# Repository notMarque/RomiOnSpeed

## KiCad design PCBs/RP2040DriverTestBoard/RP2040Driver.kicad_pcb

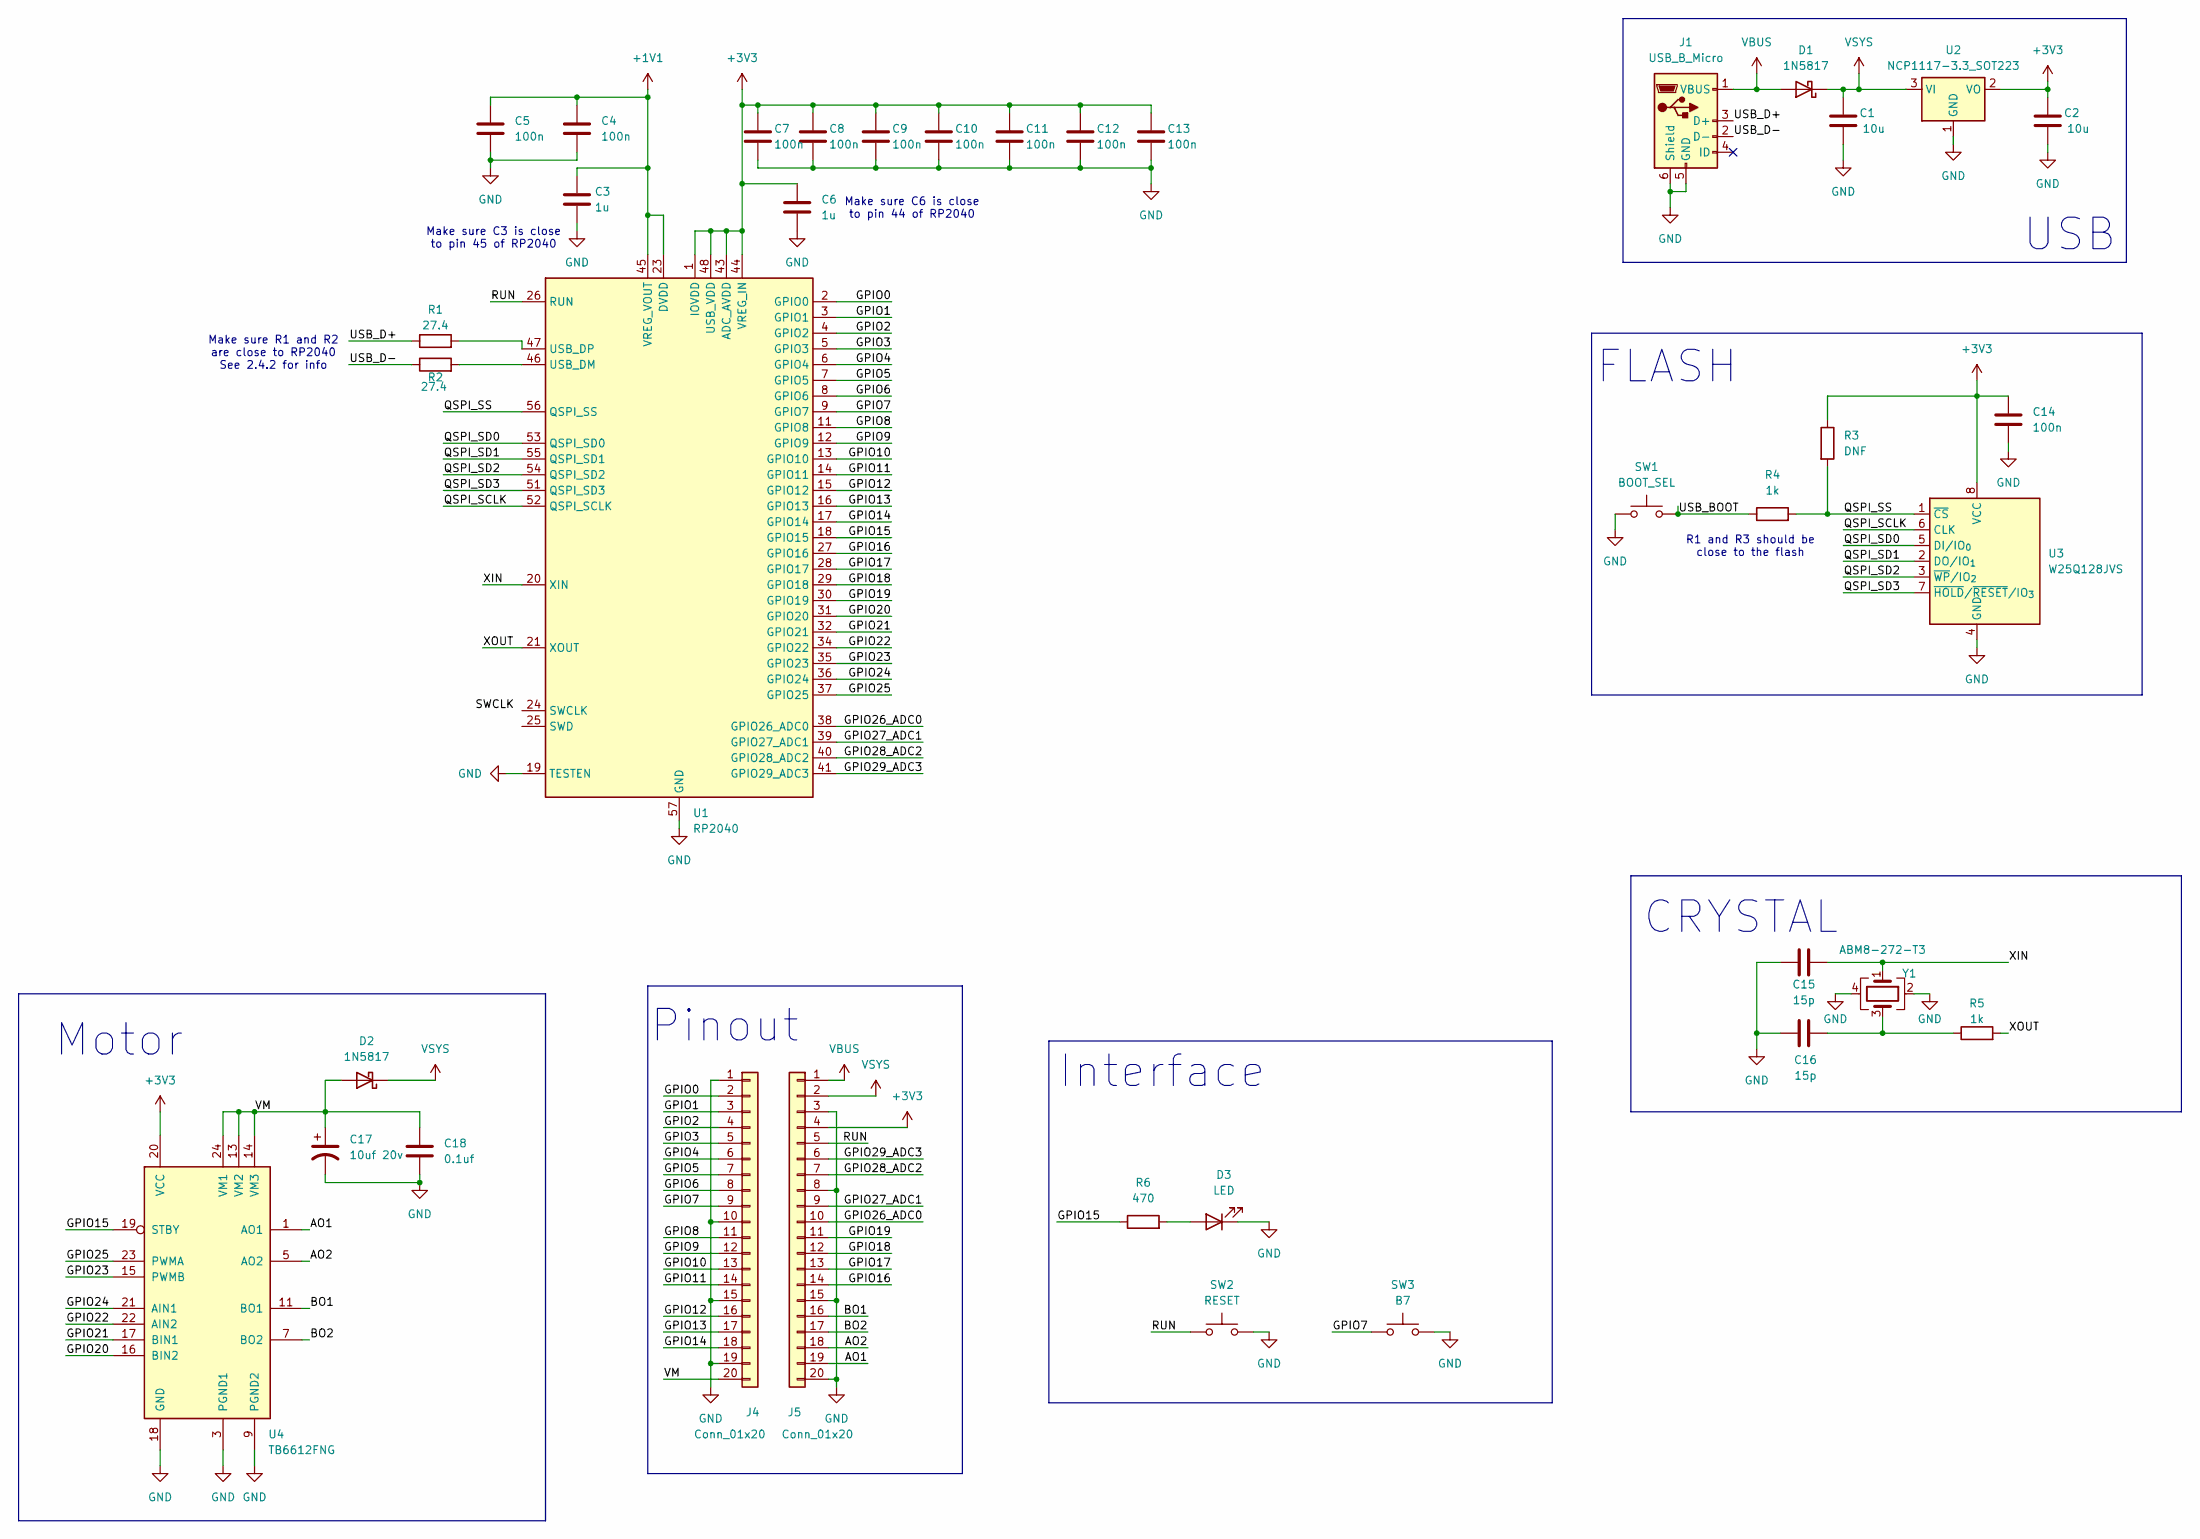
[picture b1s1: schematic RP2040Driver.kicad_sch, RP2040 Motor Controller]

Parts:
C1, C2: 10u; C_0603_1608Metric_Pad1.08x0.95mm_HandSolder
C3, C6: 1u; C_0603_1608Metric_Pad1.08x0.95mm_HandSolder
C4, C5, C7, C8, C9, C10, C11, C12, C13, C14: 100n; C_0603_1608Metric_Pad1.08x0.95mm_HandSolder
C15, C16: 15p; C_0603_1608Metric_Pad1.08x0.95mm_HandSolder
C17: 10uf 20v; C_0603_1608Metric_Pad1.08x0.95mm_HandSolder
C18: 0.1uf; C_0603_1608Metric_Pad1.08x0.95mm_HandSolder
D1, D2: 1N5817; D_0603_1608Metric_Pad1.05x0.95mm_HandSolder
D3: LED; LED_0603_1608Metric_Pad1.05x0.95mm_HandSolder
J1: USB_B_Micro; USB_Micro-B_Amphenol_10103594-0001LF_Horizontal
J4, J5: Conn_01x20; PinHeader_1x20_P2.54mm_Vertical
R1, R2: 27.4; R_0603_1608Metric_Pad0.98x0.95mm_HandSolder
R3: DNF; R_0603_1608Metric_Pad0.98x0.95mm_HandSolder
R4, R5: 1k; R_0603_1608Metric_Pad0.98x0.95mm_HandSolder
R6: 470; R_0603_1608Metric_Pad0.98x0.95mm_HandSolder
SW1: BOOT_SEL; SW_Tactile_SPST_NO_Straight_CK_PTS636Sx25SMTRLFS
SW2: RESET; SW_Tactile_SPST_NO_Straight_CK_PTS636Sx25SMTRLFS
SW3: B7; SW_Tactile_SPST_NO_Straight_CK_PTS636Sx25SMTRLFS
U1: RP2040; QFN-56-1EP_7x7mm_P0.4mm_EP3.2x3.2mm
U2: NCP1117-3.3_SOT223; SOT-223-3_TabPin2
U3: W25Q128JVS; SOIC-8_5.3x5.3mm_P1.27mm
U4: TB6612FNG; SSOP-24_5.3x8.2mm_P0.65mm
Y1: ABM8-272-T3; Crystal_SMD_Abracon_ABM8G-4Pin_3.2x2.5mm

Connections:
+1V1: C3.1, C4.1, C5.1, U1.23 (DVDD), U1.45 (VREG_VOUT), U1.50 (DVDD)
+3V3: C2.1, C6.1, C7.1, C8.1, C9.1, C10.1, C11.1, C12.1, C13.1, C14.1, J5.4, R3.1, U1.1 (IOVDD), U1.10 (IOVDD), U1.22 (IOVDD), U1.33 (IOVDD), U1.42 (IOVDD), U1.43 (ADC_AVDD), U1.44 (VREG_IN), U1.48 (USB_VDD), U1.49 (IOVDD), U2.2 (VO), U3.8 (VCC), U4.20 (VCC)
/AO1: J5.19, U4.1 (AO1), U4.2 (AO1)
/AO2: J5.18, U4.5 (AO2), U4.6 (AO2)
/BO1: J5.16, U4.11 (BO1), U4.12 (BO1)
/BO2: J5.17, U4.7 (BO2), U4.8 (BO2)
/GPIO0: J4.2, U1.2 (GPIO0)
/GPIO1: J4.3, U1.3 (GPIO1)
/GPIO2: J4.4, U1.4 (GPIO2)
/GPIO3: J4.5, U1.5 (GPIO3)
/GPIO4: J4.6, U1.6 (GPIO4)
/GPIO5: J4.7, U1.7 (GPIO5)
/GPIO6: J4.8, U1.8 (GPIO6)
/GPIO7: J4.9, SW3.1, U1.9 (GPIO7)
/GPIO8: J4.11, U1.11 (GPIO8)
/GPIO9: J4.12, U1.12 (GPIO9)
/GPIO10: J4.13, U1.13 (GPIO10)
/GPIO11: J4.14, U1.14 (GPIO11)
/GPIO12: J4.16, U1.15 (GPIO12)
/GPIO13: J4.17, U1.16 (GPIO13)
/GPIO14: J4.18, U1.17 (GPIO14)
/GPIO15: R6.1, U1.18 (GPIO15), U4.19 (STBY)
/GPIO16: J5.14, U1.27 (GPIO16)
/GPIO17: J5.13, U1.28 (GPIO17)
/GPIO18: J5.12, U1.29 (GPIO18)
/GPIO19: J5.11, U1.30 (GPIO19)
/GPIO20: U1.31 (GPIO20), U4.16 (BIN2)
/GPIO21: U1.32 (GPIO21), U4.17 (BIN1)
/GPIO22: U1.34 (GPIO22), U4.22 (AIN2)
/GPIO23: U1.35 (GPIO23), U4.15 (PWMB)
/GPIO24: U1.36 (GPIO24), U4.21 (AIN1)
/GPIO25: U1.37 (GPIO25), U4.23 (PWMA)
/GPIO26_ADC0: J5.10, U1.38 (GPIO26_ADC0)
/GPIO27_ADC1: J5.9, U1.39 (GPIO27_ADC1)
/GPIO28_ADC2: J5.7, U1.40 (GPIO28_ADC2)
/GPIO29_ADC3: J5.6, U1.41 (GPIO29_ADC3)
/QSPI_SCLK: U1.52 (QSPI_SCLK), U3.6 (CLK)
/QSPI_SD0: U1.53 (QSPI_SD0), U3.5 (DI/IO_{0})
/QSPI_SD1: U1.55 (QSPI_SD1), U3.2 (DO/IO_{1})
/QSPI_SD2: U1.54 (QSPI_SD2), U3.3 (~WP/IO_{2})
/QSPI_SD3: U1.51 (QSPI_SD3), U3.7 (~HOLD/~RESET/IO_{3})
/QSPI_SS: R3.2, R4.2, U1.56 (QSPI_SS), U3.1 (~CS)
/RUN: J5.5, SW2.1, U1.26 (RUN)
/USB_BOOT: R4.1, SW1.2
/USB_D+: J1.3 (D+), R1.1
/USB_D-: J1.2 (D-), R2.1
/VM: C17.1, C18.1, D2.2 (A), J4.20, U4.13 (VM2), U4.14 (VM3), U4.24 (VM1)
/XIN: C15.2, U1.20 (XIN), Y1.1
/XOUT: R5.2, U1.21 (XOUT)
GND: C1.2, C2.2, C3.2, C4.2, C5.2, C6.2, C7.2, C8.2, C9.2, C10.2, C11.2, C12.2, C13.2, C14.2, C15.1, C16.1, C17.2, C18.2, D3.1 (K), J1.5 (GND), J1.6 (Shield), J4.1, J4.10, J4.15, J4.19, J5.3, J5.8, J5.15, J5.20, SW1.1, SW2.2, SW3.2, U1.19 (TESTEN), U1.57 (GND), U2.1 (GND), U3.4 (GND), U4.3 (PGND1), U4.4 (PGND1), U4.9 (PGND2), U4.10 (PGND2), U4.18 (GND), Y1.2, Y1.4
unnamed: C16.2, R5.1, Y1.3
unnamed: D3.2 (A), R6.2
unnamed: R2.2, U1.46 (USB_DM)
unnamed: R1.2, U1.47 (USB_DP)
VBUS: D1.2 (A), J1.1 (VBUS), J5.1
VSYS: C1.1, D1.1 (K), D2.1 (K), J5.2, U2.3 (VI)

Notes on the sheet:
Make sure R1 and R2 are close to RP2040 See 2.4.2 for info
Interface
FLASH
Make sure C3 is close to pin 45 of RP2040
R1 and R3 should be close to the flash
CRYSTAL
Motor
USB
Pinout
Make sure C6 is close to pin 44 of RP2040

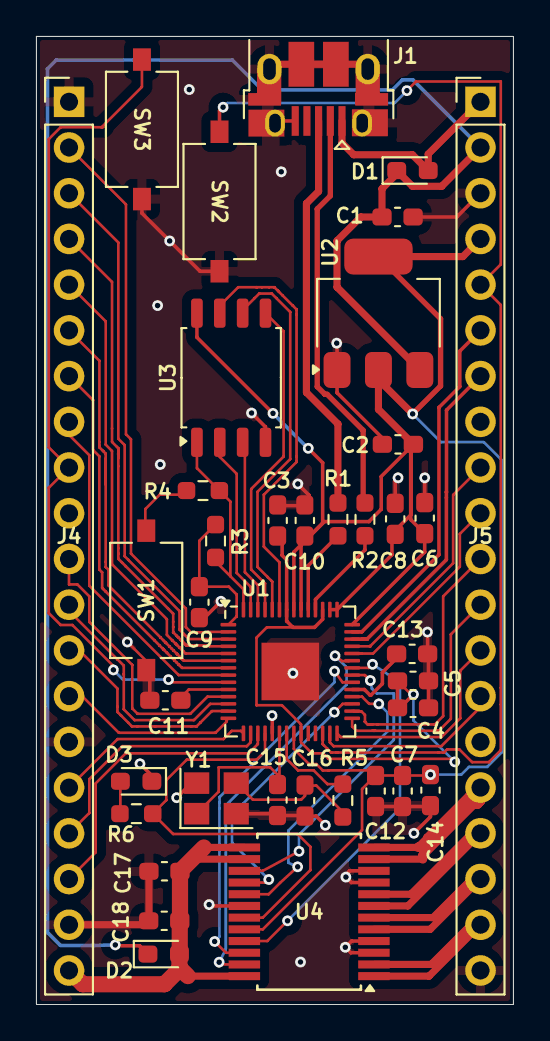
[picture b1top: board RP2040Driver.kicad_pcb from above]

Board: 2 copper layers, 26.5 x 53.8 mm, 38 parts (0 on the bottom side), 56 nets.

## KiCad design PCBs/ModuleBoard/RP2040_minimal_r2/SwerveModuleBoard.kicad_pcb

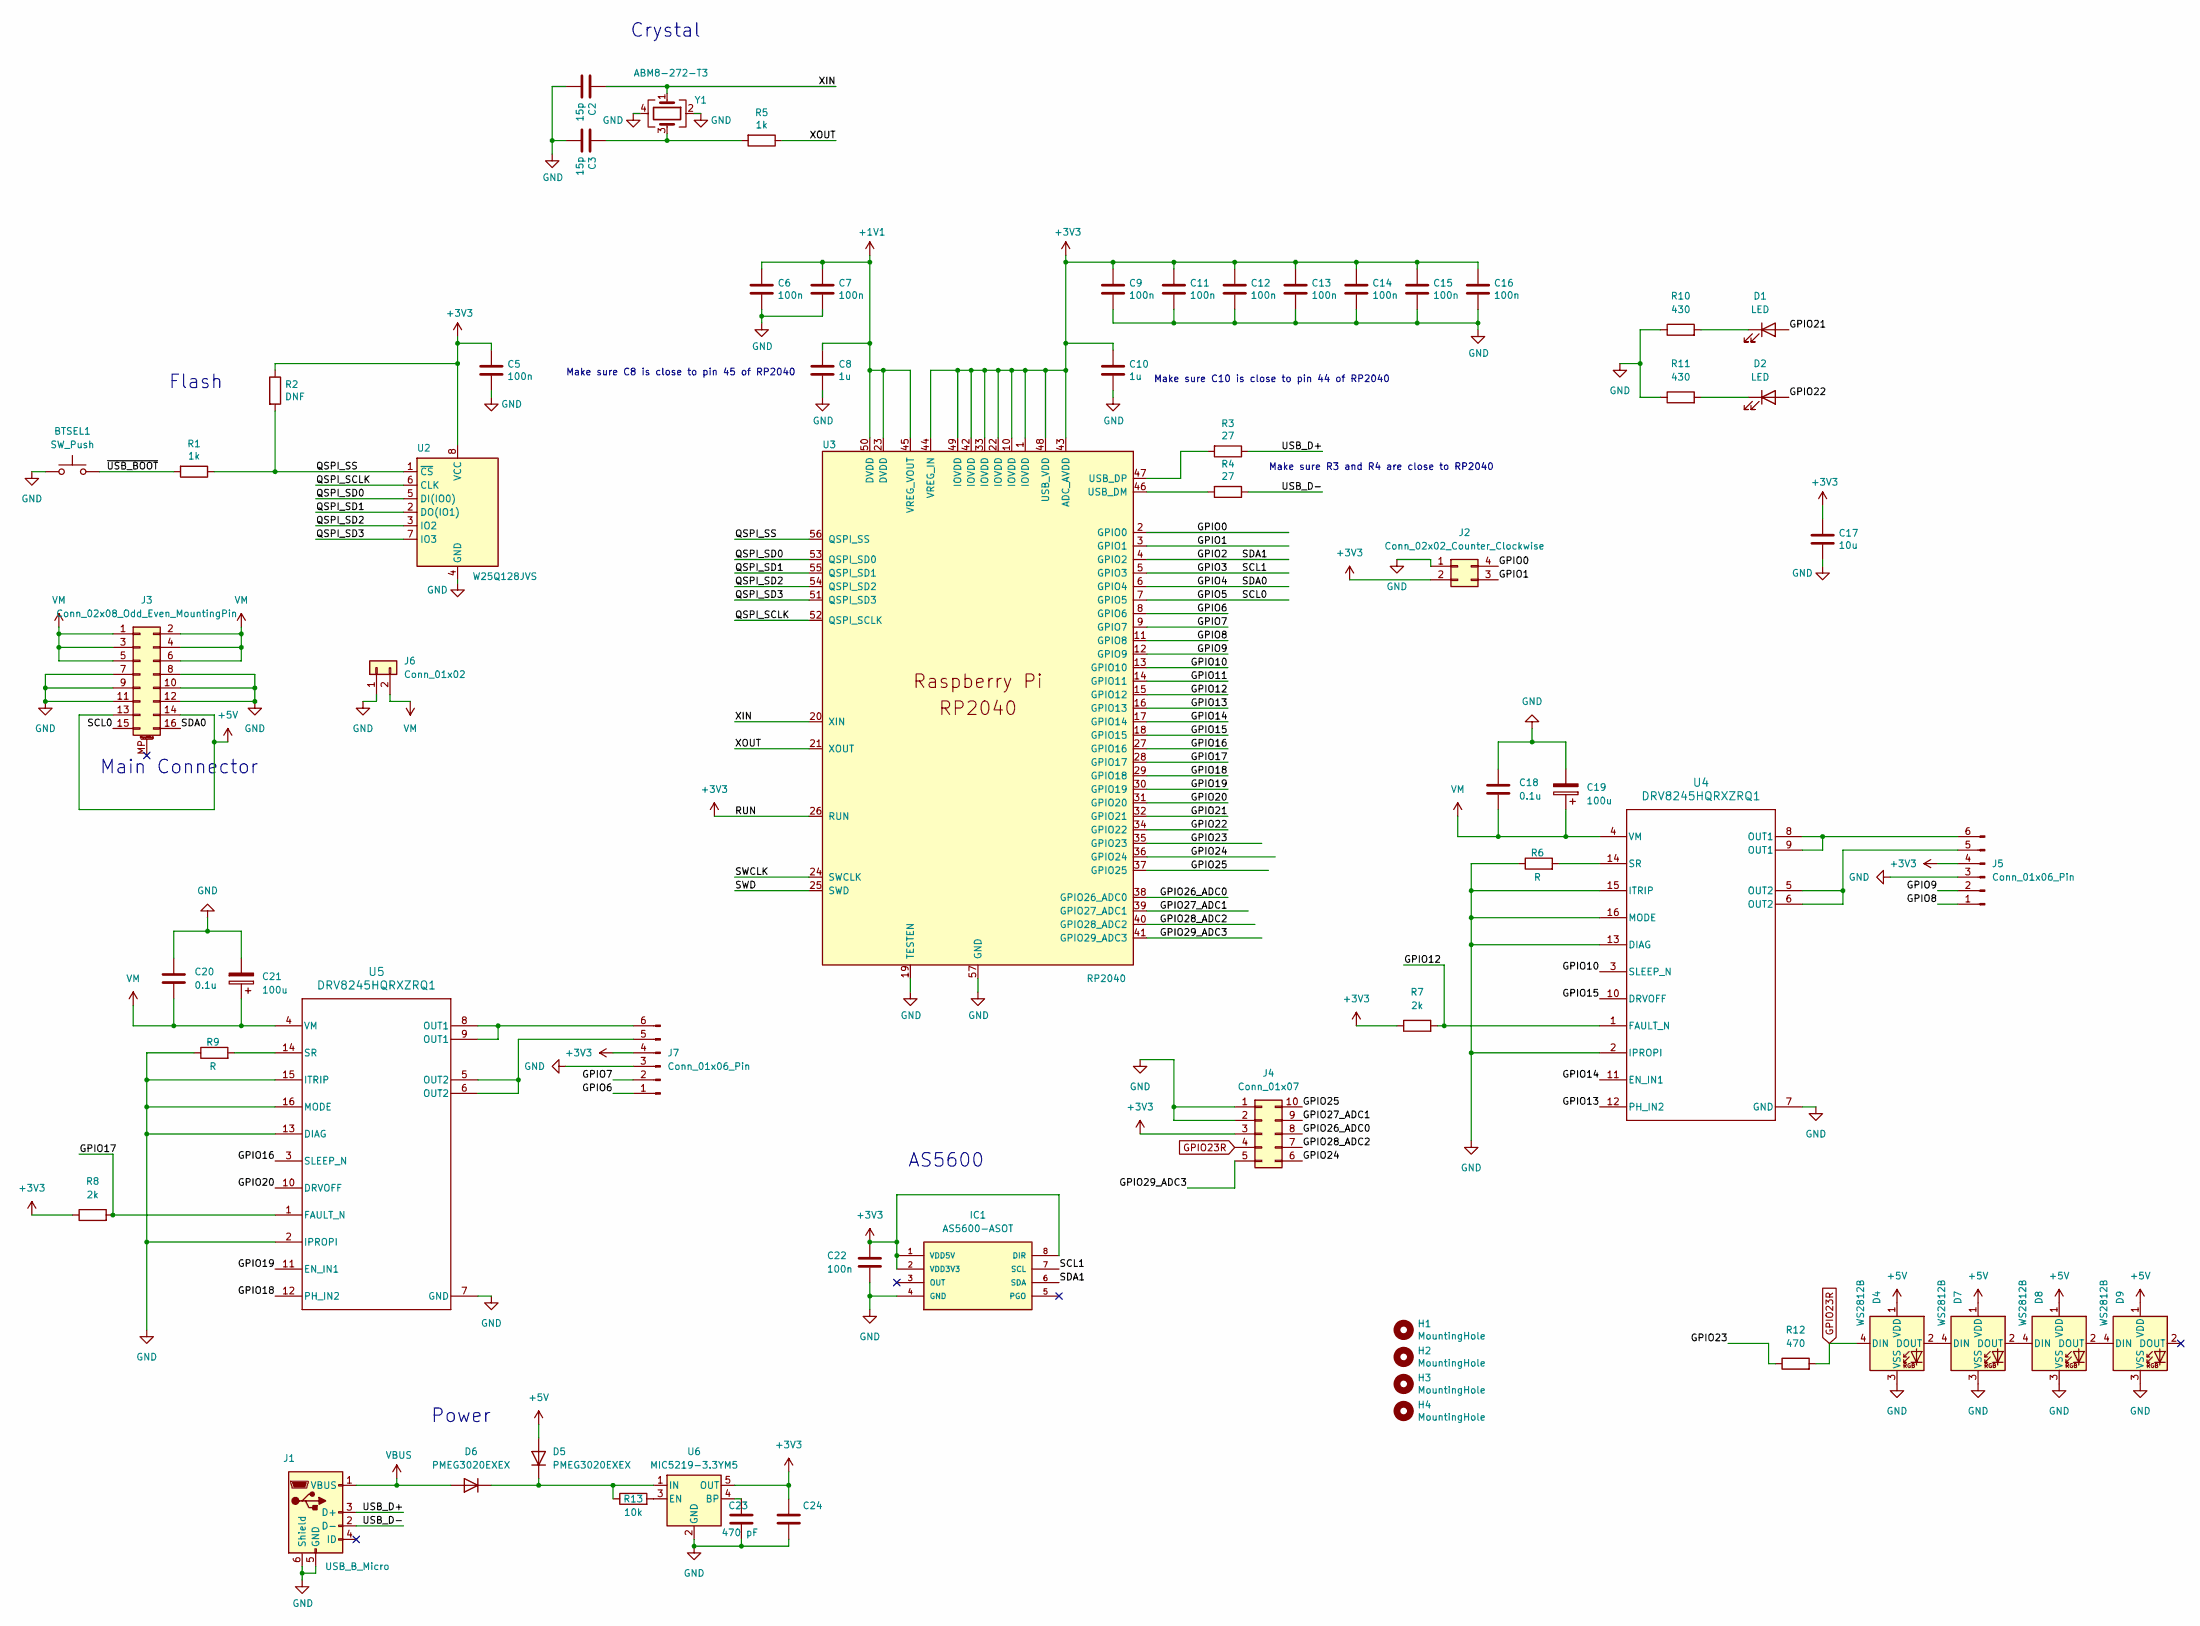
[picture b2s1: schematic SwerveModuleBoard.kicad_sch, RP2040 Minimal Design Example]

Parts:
BTSEL1: SW_Push; SW_PUSH_1P1T_6x3.5mm_H5.0_APEM_MJTP1250
C2, C3: 15p; C_0603_1608Metric_Pad1.08x0.95mm_HandSolder
C5, C6, C7, C9, C11, C12, C13, C14, C15, C16: 100n; C_0603_1608Metric_Pad1.08x0.95mm_HandSolder
C8, C10: 1u; C_0603_1608Metric_Pad1.08x0.95mm_HandSolder
C17: 10u; C_0603_1608Metric_Pad1.08x0.95mm_HandSolder
C18, C20: 0.1u; C_0603_1608Metric_Pad1.08x0.95mm_HandSolder
C19, C21: 100u; CAPAE800X700
C22: 100n; C_0603_1608Metric
C23: 470 pF; C_0603_1608Metric
C24: 22 uF; C_1206_3216Metric_Pad1.33x1.80mm_HandSolder
D1, D2: LED; LED_0603_1608Metric_Pad1.05x0.95mm_HandSolder
D4, D7, D8, D9: WS2812B; LED_WS2812B_PLCC4_5.0x5.0mm_P3.2mm
D5, D6: PMEG3020EXEX; D_SOD-123F
H1, H2, H3, H4: MountingHole; MountingHole_3.2mm_M3_DIN965_Pad_TopBottom
IC1: AS5600-ASOT; SOIC-8_3.9x4.9mm_P1.27mm; MOUSER_PART_NUMBER 985-AS5600-ASOT
J1: USB_B_Micro; USB_Micro-B_Amphenol_10103594-0001LF_Horizontal_modified
J2: Conn_02x02_Counter_Clockwise; PinHeader_2x02_P2.54mm_Vertical
J3: Conn_02x08_Odd_Even_MountingPin; PinHeader_2x08_P2.54mm_Vertical
J4: Conn_01x07; PinHeader_2x05_P2.54mm_Vertical
J5, J7: Conn_01x06_Pin; PinHeader_1x06_P2.54mm_Vertical
J6: Conn_01x02; AMASS_XT30U-M_1x02_P5.0mm_Vertical
R1, R5: 1k; R_0603_1608Metric_Pad0.98x0.95mm_HandSolder
R2: DNF; R_0603_1608Metric_Pad0.98x0.95mm_HandSolder
R3, R4: 27; R_0603_1608Metric_Pad0.98x0.95mm_HandSolder
R6, R9: R; R_0603_1608Metric_Pad0.98x0.95mm_HandSolder
R7, R8: 2k; R_0603_1608Metric_Pad0.98x0.95mm_HandSolder
R10, R11: 430; R_0603_1608Metric_Pad0.98x0.95mm_HandSolder
R12: 470; C_0603_1608Metric_Pad1.08x0.95mm_HandSolder
R13: 10k; R_0603_1608Metric
U2: W25Q128JVS; SOIC-8_5.3x5.3mm_P1.27mm
U3: RP2040; RP2040-QFN-56
U4, U5: DRV8245HQRXZRQ1; RXZ0016A-MFG
U6: MIC5219-3.3YM5; SOT-23-5
Y1: ABM8-272-T3; Crystal_SMD_3225-4Pin_3.2x2.5mm

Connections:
+1V1: C6.1, C7.1, C8.1, U3.23 (DVDD), U3.45 (VREG_VOUT), U3.50 (DVDD)
+3V3: C5.1, C9.1, C10.1, C11.1, C12.1, C13.1, C14.1, C15.1, C16.1, C17.1, C22.1, C24.1, IC1.1 (VDD5V), IC1.2 (VDD3V3), IC1.8 (DIR), J2.2, J4.3, J5.4, J7.4, R2.1, R7.1, R8.1, U2.8 (VCC), U3.1 (IOVDD), U3.10 (IOVDD), U3.22 (IOVDD), U3.26 (RUN), U3.33 (IOVDD), U3.42 (IOVDD), U3.43 (ADC_AVDD), U3.44 (VREG_IN), U3.48 (USB_VDD), U3.49 (IOVDD), U6.5 (OUT)
+5V: D4.1 (VDD), D5.2 (A), D7.1 (VDD), D8.1 (VDD), D9.1 (VDD), J3.13, J3.14
/GPIO0: J2.4, U3.2 (GPIO0)
/GPIO1: J2.3, U3.3 (GPIO1)
/GPIO2: IC1.6 (SDA), U3.4 (GPIO2)
/GPIO3: IC1.7 (SCL), U3.5 (GPIO3)
/GPIO4: J3.16, U3.6 (GPIO4)
/GPIO5: J3.15, U3.7 (GPIO5)
/GPIO6: J7.1, U3.8 (GPIO6)
/GPIO7: J7.2, U3.9 (GPIO7)
/GPIO8: J5.1, U3.11 (GPIO8)
/GPIO9: J5.2, U3.12 (GPIO9)
/GPIO10: U3.13 (GPIO10), U4.3 (SLEEP_N)
/GPIO11: U3.14 (GPIO11)
/GPIO12: R7.2, U3.15 (GPIO12), U4.1 (FAULT_N)
/GPIO13: U3.16 (GPIO13), U4.12 (PH_IN2)
/GPIO14: U3.17 (GPIO14), U4.11 (EN_IN1)
/GPIO15: U3.18 (GPIO15), U4.10 (DRVOFF)
/GPIO16: U3.27 (GPIO16), U5.3 (SLEEP_N)
/GPIO17: R8.2, U3.28 (GPIO17), U5.1 (FAULT_N)
/GPIO18: U3.29 (GPIO18), U5.12 (PH_IN2)
/GPIO19: U3.30 (GPIO19), U5.11 (EN_IN1)
/GPIO20: U3.31 (GPIO20), U5.10 (DRVOFF)
/GPIO21: D1.2 (A), U3.32 (GPIO21)
/GPIO22: D2.2 (A), U3.34 (GPIO22)
/GPIO23: R12.1, U3.35 (GPIO23)
/GPIO24: J4.6, U3.36 (GPIO24)
/GPIO25: J4.10, U3.37 (GPIO25)
/GPIO26_ADC0: J4.8, U3.38 (GPIO26_ADC0)
/GPIO27_ADC1: J4.9, U3.39 (GPIO27_ADC1)
/GPIO28_ADC2: J4.7, U3.40 (GPIO28_ADC2)
/GPIO29_ADC3: J4.5, U3.41 (GPIO29_ADC3)
/QSPI_SCLK: U2.6 (CLK), U3.52 (QSPI_SCLK)
/QSPI_SD0: U2.5 (DI(IO0)), U3.53 (QSPI_SD0)
/QSPI_SD1: U2.2 (DO(IO1)), U3.55 (QSPI_SD1)
/QSPI_SD2: U2.3 (IO2), U3.54 (QSPI_SD2)
/QSPI_SD3: U2.7 (IO3), U3.51 (QSPI_SD3)
/QSPI_SS: R1.1, R2.2, U2.1 (~CS), U3.56 (QSPI_SS)
/SWCLK: U3.24 (SWCLK)
/SWD: U3.25 (SWD)
/USB_D+: J1.3 (D+), R3.1
/USB_D-: J1.2 (D-), R4.1
/XIN: C2.1, U3.20 (XIN), Y1.1
/XOUT: R5.1, U3.21 (XOUT)
/~USB_BOOT: BTSEL1.2, R1.2
GND: BTSEL1.1, C2.2, C3.2, C5.2, C6.2, C7.2, C8.2, C9.2, C10.2, C11.2, C12.2, C13.2, C14.2, C15.2, C16.2, C17.2, C18.1, C19.2, C20.1, C21.2, C22.2, C23.2, C24.2, D4.3 (VSS), D7.3 (VSS), D8.3 (VSS), D9.3 (VSS), IC1.4 (GND), J1.5 (GND), J1.6 (Shield), J2.1, J3.7, J3.8, J3.9, J3.10, J3.11, J3.12, J4.1, J4.2, J5.3, J6.1, J7.3, R6.1, R9.1, R10.1, R11.1, U2.4 (GND), U3.19 (TESTEN), U3.57 (GND), U4.2 (IPROPI), U4.7 (GND), U4.13 (DIAG), U4.15 (ITRIP), U4.16 (MODE), U5.2 (IPROPI), U5.7 (GND), U5.13 (DIAG), U5.15 (ITRIP), U5.16 (MODE), U6.2 (GND), Y1.2, Y1.4
GPIO23R: D4.4 (DIN), J4.4, R12.2
unnamed: C3.1, R5.2, Y1.3
unnamed: D1.1 (K), R10.2
unnamed: D2.1 (K), R11.2
unnamed: D4.2 (DOUT), D7.4 (DIN)
unnamed: D5.1 (K), D6.1 (K), R13.1, U6.1 (IN)
unnamed: D7.2 (DOUT), D8.4 (DIN)
unnamed: D8.2 (DOUT), D9.4 (DIN)
unnamed: J5.5, U4.5 (OUT2), U4.6 (OUT2)
unnamed: J5.6, U4.8 (OUT1), U4.9 (OUT1)
unnamed: J7.5, U5.5 (OUT2), U5.6 (OUT2)
unnamed: J7.6, U5.8 (OUT1), U5.9 (OUT1)
unnamed: R4.2, U3.46 (USB_DM)
unnamed: R3.2, U3.47 (USB_DP)
unnamed: R6.2, U4.14 (SR)
unnamed: R9.2, U5.14 (SR)
unnamed: C23.1, U6.4 (BP)
unnamed: R13.2, U6.3 (EN)
VBUS: D6.2 (A), J1.1 (VBUS)
VM: C18.2, C19.1, C20.2, C21.1, J3.1, J3.2, J3.3, J3.4, J3.5, J3.6, J6.2, U4.4 (VM), U5.4 (VM)

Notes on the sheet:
Power
Crystal
Make sure C8 is close to pin 45 of RP2040
Make sure C10 is close to pin 44 of RP2040
Main Connector
Make sure R3 and R4 are close to RP2040
AS5600
Flash

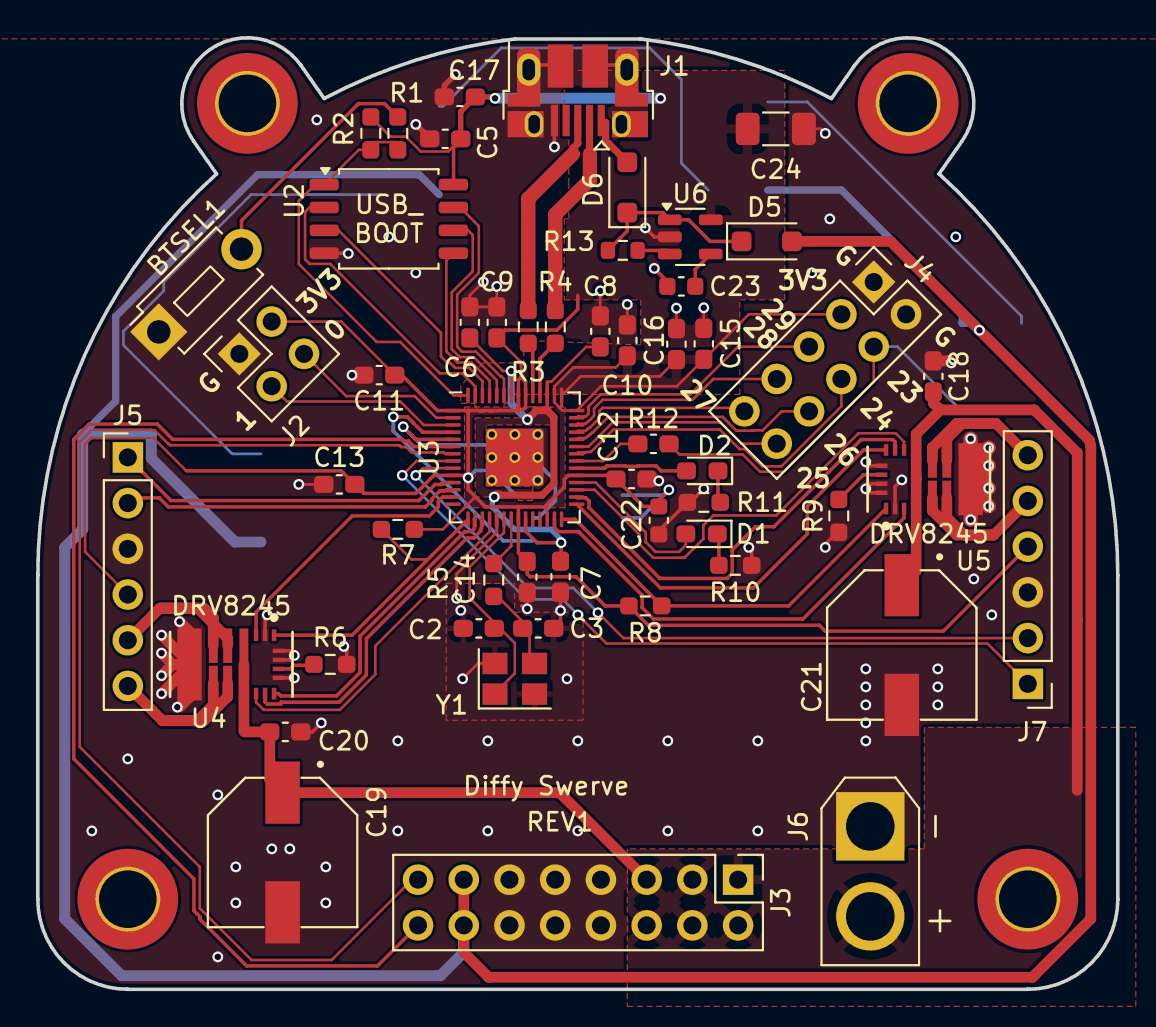
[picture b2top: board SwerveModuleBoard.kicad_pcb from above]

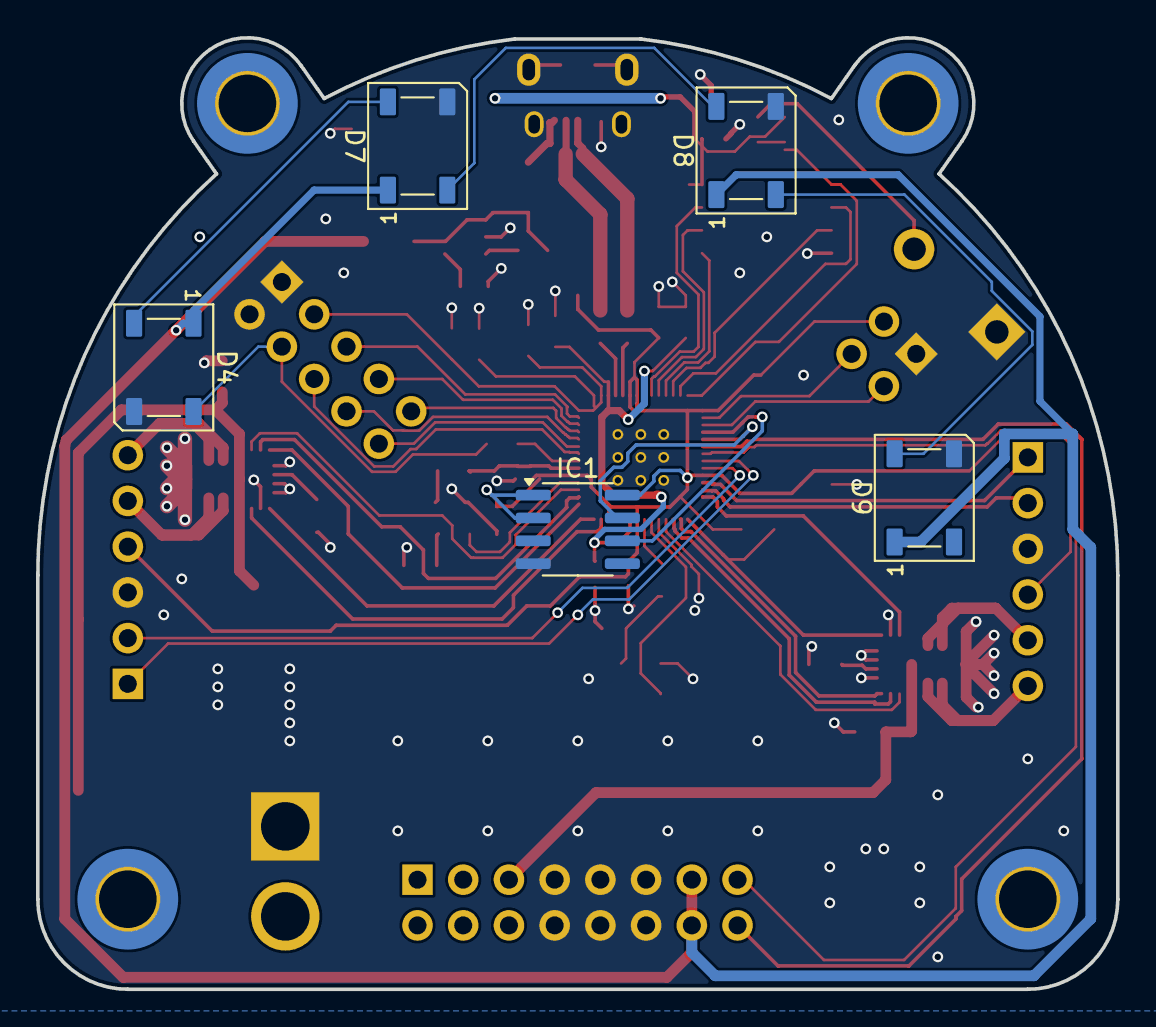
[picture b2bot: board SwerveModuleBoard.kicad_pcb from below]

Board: 2 copper layers, 60.0 x 52.9 mm, 62 parts (5 on the bottom side), 64 nets.

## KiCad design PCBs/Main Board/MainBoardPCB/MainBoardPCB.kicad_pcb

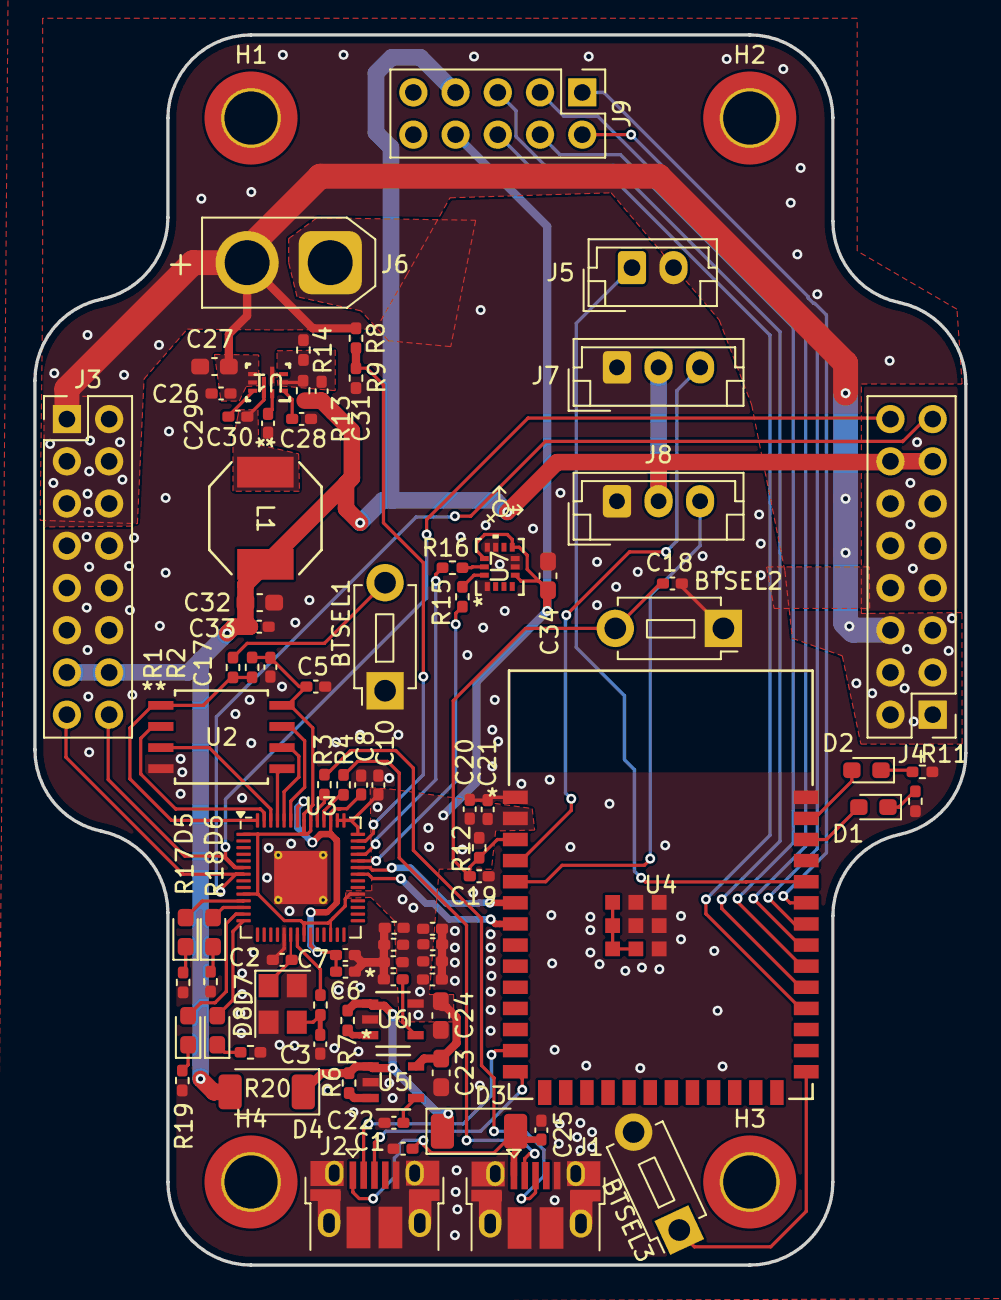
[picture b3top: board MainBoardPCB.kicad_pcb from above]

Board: 4 copper layers, 56.0 x 74.0 mm, 87 parts (0 on the bottom side), 64 nets.

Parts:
BTSEL1, BTSEL2, BTSEL3: SW_Push; SW_PUSH_1P1T_6x3.5mm_H5.0_APEM_MJTP1250
C1, C17, C25: 10u; C_0402_1005Metric_Pad0.74x0.62mm_HandSolder
C2, C3: 15p; C_0402_1005Metric_Pad0.74x0.62mm_HandSolder
C4, C22: 470 pF; C_0402_1005Metric_Pad0.74x0.62mm_HandSolder
C5, C6, C7, C9, C11, C12, C13, C14, C15, C16: 100n; C_0402_1005Metric_Pad0.74x0.62mm_HandSolder
C8, C10: 1u; C_0402_1005Metric_Pad0.74x0.62mm_HandSolder
C18, C19, C20: 22μF; C_0402_1005Metric_Pad0.74x0.62mm_HandSolder
C21, C26, C30, C33: 100 nF; C_0402_1005Metric_Pad0.74x0.62mm_HandSolder
C23, C24, C32, C34: 22 uF; C_0603_1608Metric_Pad1.08x0.95mm_HandSolder
C27: 47 uF; C_0603_1608Metric_Pad1.08x0.95mm_HandSolder
C28: 1 uF; C_0402_1005Metric_Pad0.74x0.62mm_HandSolder
C29: 10 nF; C_0402_1005Metric_Pad0.74x0.62mm_HandSolder
C31: 33 pF; C_0402_1005Metric_Pad0.74x0.62mm_HandSolder
D1, D2, D5, D6, D7, D8: LED; LED_0603_1608Metric_Pad1.05x0.95mm_HandSolder
D3, D4: PMEG3020EXEX; D_SOD-128
H1, H2, H3, H4: MountingHole; MountingHole_3.2mm_M3_DIN965_Pad_TopBottom
J1, J2: USB_B_Micro; USB_Micro-B_Amphenol_10103594-0001LF_Horizontal
J3, J4: Conn_02x08_Odd_Even_MountingPin; PinHeader_2x08_P2.54mm_Vertical
J5: Conn_01x02; JST_EH_B2B-EH-A_1x02_P2.50mm_Vertical
J6: Conn_01x02; AMASS_XT30U-M_1x02_P5.0mm_Vertical
J7, J8: Conn_01x03; JST_EH_B3B-EH-A_1x03_P2.50mm_Vertical
J9: Conn_02x05_Counter_Clockwise; PinHeader_2x05_P2.54mm_Vertical
L1: L; IND_SPM6530_TDK
R1, R5: 1k; R_0402_1005Metric_Pad0.72x0.64mm_HandSolder
R2: DNF; R_0402_1005Metric_Pad0.72x0.64mm_HandSolder
R3, R4: 27; R_0402_1005Metric_Pad0.72x0.64mm_HandSolder
R6, R7, R12, R15, R16: 10k; R_0402_1005Metric_Pad0.72x0.64mm_HandSolder
R8: 100k; R_0402_1005Metric_Pad0.72x0.64mm_HandSolder
R9: 20k; R_0402_1005Metric_Pad0.72x0.64mm_HandSolder
R10, R11, R17, R18, R19, R20: 430; R_0402_1005Metric_Pad0.72x0.64mm_HandSolder
R13: 220k; R_0402_1005Metric_Pad0.72x0.64mm_HandSolder
R14: 30k; R_0402_1005Metric_Pad0.72x0.64mm_HandSolder
U1: TPS566238PRQFR; RQF0009A
U2: W25Q128JVS; SOIC_128JVSIQ_WIN
U3: RP2040; QFN-56-1EP_7x7mm_P0.4mm_EP3.2x3.2mm_ThermalVias
U4: ESP32-S3-WROOM-1-N16; ESP32-S3-WROOM-1_EXP
U5, U6: MIC5219-3.3YM5; MIC
U7: LSM6DSVTR; LGA14-L_2P59X3P1X0P5_STM
Y1: ABM8-272-T3; Crystal_SMD_3225-4Pin_3.2x2.5mm

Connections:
2040RX: U3.37 (GPIO25), U4.6 (IO6)
2040TX: U3.36 (GPIO24), U4.7 (IO7)
+1V1: C6.1, C7.1, C8.1, U3.23 (DVDD), U3.45 (VREG_VOUT), U3.50 (DVDD)
+3V3: C5.1, C9.1, C10.1, C11.1, C12.1, C13.1, C14.1, C15.1, C16.1, C17.1, C20.2, C21.2, C23.1, C24.1, C34.1, J9.8, R2.1, R12.2, U2.8 (VCC), U3.1 (IOVDD), U3.10 (IOVDD), U3.22 (IOVDD), U3.26 (RUN), U3.33 (IOVDD), U3.42 (IOVDD), U3.43 (ADC_AVDD), U3.44 (VREG_IN), U3.48 (USB_VDD), U3.49 (IOVDD), U4.2 (3V3), U5.5 (OUT), U6.5 (OUT), U7.5 (VDD_IO), U7.8 (VDD), U7.12 (CS)
+5V: C31.1, C32.1, C33.1, D4.2 (A), J3.13, J3.14, J4.13, J4.14, J7.2, J8.2, J9.7, L1.2, R13.2
/GPIO4: J3.16, J4.16, U3.6 (GPIO4)
/GPIO5: J3.15, J4.15, U3.7 (GPIO5)
/QSPI_SCLK: U2.6 (CLK), U3.52 (QSPI_SCLK)
/QSPI_SD0: U2.5 (DI(IO0)), U3.53 (QSPI_SD0)
/QSPI_SD1: U2.2 (DO(IO1)), U3.55 (QSPI_SD1)
/QSPI_SD2: U2.3 (IO2), U3.54 (QSPI_SD2)
/QSPI_SD3: U2.7 (IO3), U3.51 (QSPI_SD3)
/QSPI_SS: R1.1, R2.2, U2.1 (~CS), U3.56 (QSPI_SS)
/USB_D+: J1.3 (D+), R3.1
/USB_D-: J1.2 (D-), R4.1
/XIN: C2.1, U3.20 (XIN), Y1.1
/XOUT: R5.1, U3.21 (XOUT)
/~USB_BOOT: BTSEL1.2, R1.2
BATT_READ: R8.2, R9.1, U3.41 (GPIO29_ADC3)
D+: J2.3 (D+), U4.14 (IO20)
D-: J2.2 (D-), U4.13 (IO19)
GND: BTSEL1.1, BTSEL2.1, BTSEL3.2, C1.2, C2.2, C3.2, C4.2, C5.2, C6.2, C7.2, C8.2, C9.2, C10.2, C11.2, C12.2, C13.2, C14.2, C15.2, C16.2, C17.2, C18.1, C19.2, C20.1, C21.1, C22.2, C23.2, C24.2, C25.2, C26.2, C27.2, C28.2, C29.2, C32.2, C33.2, C34.2, J1.5 (GND), J1.6 (Shield), J2.5 (GND), J2.6 (Shield), J3.7, J3.8, J3.9, J3.10, J3.11, J3.12, J4.7, J4.8, J4.9, J4.10, J4.11, J4.12, J5.2, J6.1, J7.1, J8.1, J9.9, J9.10, R9.2, R10.1, R11.1, R14.1, R17.1, R18.1, R19.1, R20.1, U1.4 (PGND), U2.4 (GND), U3.19 (TESTEN), U3.57 (GND), U4.1 (GND), U4.40 (GND), U4.41 (GND), U4.46 (GND), U4.47 (GND), U4.48 (GND), U4.49 (GND), U5.2 (GND), U6.2 (GND), U7.1 (SDO/SA0), U7.6 (GND), U7.7 (GND), U7.10 (OCS_AUX), U7.11 (SDO_AUX), Y1.2, Y1.4
GYROSCL: R16.1, U3.39 (GPIO27_ADC1)
GYROSDA: R15.1, U3.38 (GPIO26_ADC0)
LED1: D2.2 (A), U4.39 (IO1)
LED2: D1.2 (A), U4.38 (IO2)
LED3: D5.2 (A), U3.11 (GPIO8)
LED4: D6.2 (A), U3.12 (GPIO9)
LED5: D7.2 (A), U3.13 (GPIO10)
LED6: D8.2 (A), U3.14 (GPIO11)
unnamed: C3.1, R5.2, Y1.3
unnamed: D1.1 (K), R10.2
unnamed: D2.1 (K), R11.2
unnamed: D3.1 (K), D4.1 (K), R6.1, R7.1, U5.1 (IN), U6.1 (IN)
unnamed: D5.1 (K), R17.2
unnamed: D6.1 (K), R18.2
unnamed: D7.1 (K), R19.2
unnamed: D8.1 (K), R20.2
unnamed: J9.1, U4.35 (IO42)
unnamed: J9.2, U4.34 (IO41)
unnamed: J9.3, U4.33 (IO40)
unnamed: J9.4, U4.32 (IO39)
unnamed: J9.5, U4.31 (IO38)
unnamed: J9.6, U4.30 (IO37)
unnamed: C30.1, U1.7 (BST)
unnamed: C31.2, R13.1, R14.2, U1.2 (FB)
unnamed: C29.1, U1.9 (SS)
unnamed: C30.2, L1.1, U1.8 (SW)
unnamed: C28.1, U1.1 (VCC)
unnamed: R4.2, U3.46 (USB_DM)
unnamed: R3.2, U3.47 (USB_DP)
unnamed: BTSEL2.2, C18.2, C19.1, R12.1, U4.3 (EN)
unnamed: BTSEL3.1, U4.27 (IO0)
unnamed: C22.1, U5.4 (BP)
unnamed: R6.2, U5.3 (EN)
unnamed: C4.1, U6.4 (BP)
unnamed: R7.2, U6.3 (EN)
unnamed: R16.2, U7.13 (SCL)
unnamed: R15.2, U7.14 (SDA)
RX: J5.1, U4.36 (RXD0)
Servo1: J7.3, U4.4 (IO4)
Servo2: J8.3, U4.5 (IO5)
VAA: C26.1, C27.1, J3.1, J3.2, J3.3, J3.4, J3.5, J3.6, J4.1, J4.2, J4.3, J4.4, J4.5, J4.6, J6.2, R8.1, U1.5 (VIN), U1.6 (VIN)
VUSB: C1.1, C25.1, D3.2 (A), J1.1 (VBUS), J2.1 (VBUS)
